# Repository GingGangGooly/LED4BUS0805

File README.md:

LED4BUS0805
===========

4 x 0805 LED's prototype breakout with 0.1" headers

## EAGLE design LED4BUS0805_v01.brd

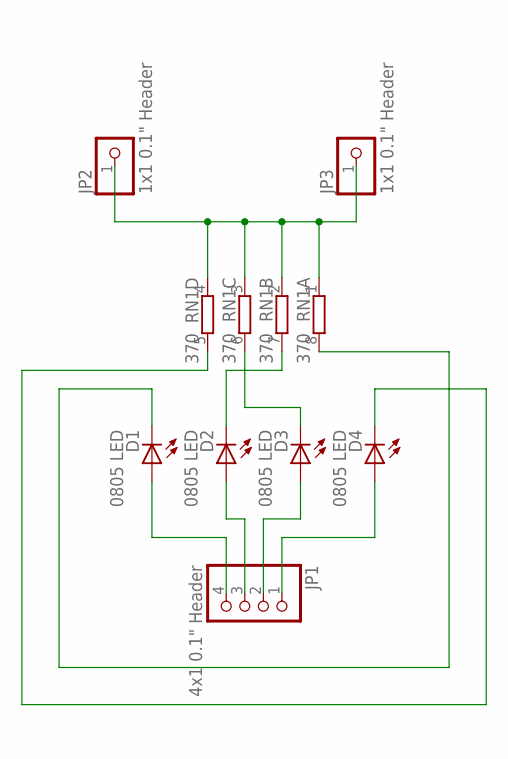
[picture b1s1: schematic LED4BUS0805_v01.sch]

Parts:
D1, D2, D3, D4: 0805 LED; CHIP-LED0805
JP1: 4x1 0.1" Header; 1X04
JP2, JP3: 1x1 0.1" Header; 1X01
RN1: 370; 0603-ARV

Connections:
unnamed: D2.A, JP1.3
unnamed: D3.A, JP1.2
unnamed: D4.A, JP1.1
unnamed: D1.A, JP1.4
unnamed: D3.C, RN1.6 (2)
unnamed: D2.C, RN1.7 (2)
unnamed: D4.C, RN1.5 (2)
unnamed: D1.C, RN1.8 (2)
unnamed: JP2.1, JP3.1, RN1.1, RN1.2 (1), RN1.3 (1), RN1.4 (1)

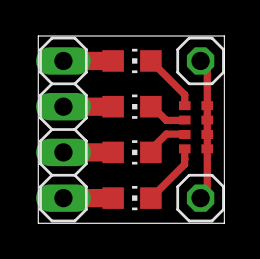
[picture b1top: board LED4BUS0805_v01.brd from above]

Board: 2 copper layers, 10.3 x 10.4 mm, 8 parts (0 on the bottom side), 9 nets.

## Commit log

2014-07-30 :neckbeard: Added .gitattributes & .gitignore files
2014-07-30 LED4BUS0805 initial deposit
2014-07-30 Revert "LED4BUS0805 initial deposit"
    This reverts commit 451fb03e5ad89676a61fab92d2c2b56c2c164013.
2014-07-30 EAGLE PCB
2014-07-30 EAGLE Schematic

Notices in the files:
LED4BUS0805_v01.brd:
(c) 2013
